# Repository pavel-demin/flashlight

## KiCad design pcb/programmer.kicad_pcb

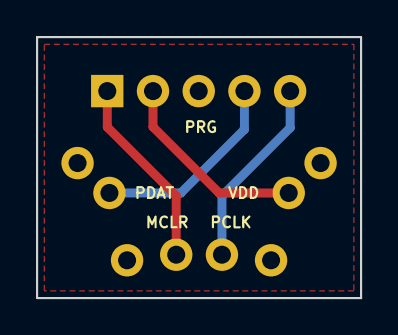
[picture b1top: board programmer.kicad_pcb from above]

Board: 2 copper layers, 18.0 x 14.5 mm, 9 parts (0 on the bottom side), 5 nets.

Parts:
MCLR: MCLR; PIN-1.0mm
PCLK: PCLK; PIN-1.0mm
PDAT: PDAT; PIN-1.0mm
PIN1, PIN2, PIN3, PIN4: PIN; PIN-1.0mm
PRG: PRG; Pin_Header_Straight_1x05_Pitch2.54mm
VDD: VDD; PIN-1.0mm

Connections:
GND: PIN1.1, PIN2.1, PIN3.1, PIN4.1, PRG.3
unnamed: PRG.2, VDD.1
unnamed: PCLK.1, PRG.5
unnamed: PDAT.1, PRG.4
unnamed: MCLR.1, PRG.1

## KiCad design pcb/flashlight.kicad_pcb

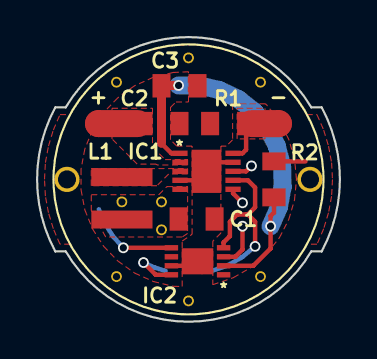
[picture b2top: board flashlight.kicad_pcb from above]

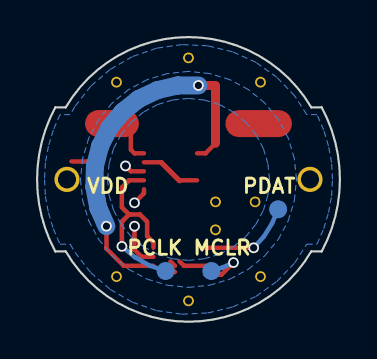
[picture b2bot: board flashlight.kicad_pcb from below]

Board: 2 copper layers, 16.8 x 15.8 mm, 25 parts (4 on the bottom side), 9 nets.

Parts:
+: +LED; PAD-1.5mm
-: LED-; PAD-1.5mm
C1: 10u; 0805
C2: 22u; 0805
C3: 1u; 0805
IC1: TPS61200; DRC
IC2: PIC10F320; MC
L1: 2.2u; XFL4020
MCLR: MCLR; PAD-1.0mm
PCLK: PCLK; PAD-1.0mm
PDAT: PDAT; PAD-1.0mm
PIN1, PIN2: PIN; PIN-1.0mm
R1: 2; 0805
R2: 1M; 0805
VDD: VDD; PAD-1.0mm
VIA1, VIA2, VIA3, VIA4, VIA5, VIA6, VIA7, VIA8, VIA9: VIA; VIA-0.6mm

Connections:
GND: C1.2, C2.2, C3.2, IC1.4, IC1.9, IC1.11, IC2.7, IC2.9, PIN1.1, PIN2.1, R1.2, R2.1, VIA4.1, VIA5.1, VIA6.1, VIA7.1, VIA8.1, VIA9.1
unnamed: IC1.3, L1.2
unnamed: +.1, C2.1, IC1.2
unnamed: C3.1, IC1.1, IC2.2, R2.2, VDD.1
unnamed: IC1.7, IC2.4, PCLK.1
unnamed: -.1, IC1.10, R1.1
unnamed: IC2.5, PDAT.1
unnamed: IC2.8, MCLR.1
SUPPLY: C1.1, IC1.5, IC1.6, IC1.8, IC2.3, L1.1, VIA1.1, VIA2.1, VIA3.1

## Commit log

2017-03-05 add flashlight.c
2017-03-05 set pcb radius to 7.9 mm
2017-03-05 add configuration bits
2017-03-06 add PIN-1.0mm
2017-03-06 add PIN part
2017-03-06 add two pins
2017-03-06 reduce VIA-0.6mm fonts
2017-03-06 move programming pads to bottom and add support extensions
2017-03-07 reduce radius of supply mask and move supply vias
2017-03-07 increase reference font size
2017-03-07 increase width of the vdd and led traces
2017-03-07 enlarge gnd zone
2017-03-07 reduce number of corners in circular zones
2017-03-08 add flashlight.asm
2017-03-09 remove extra empty line from flashlight.asm
2017-03-10 reduce delay in flashlight.asm
2017-03-11 add battery undervoltage protection
2017-03-11 set TRISA bit for RA3
2017-03-11 measure supply voltage 30 times per second
2017-03-11 replace CBLOCK with UDATA
2017-03-11 use timer interrupt for debouncing
2017-03-11 simplify mode switching
2017-03-12 set clock frequency to 1 MHz, remove interrupt code and add subroutines
2017-03-12 replace INTCON,2 with INTCON,TMR0IF
2017-03-12 replace busy loops with sleep
2017-03-13 fix TRISA and ANSELA, disable FVR after measurements
2017-03-13 replace 10k with 470k
2017-03-14 add flashlight-pwm.asm
2017-04-02 connect R2 to GND
2017-04-02 set RA1 to high in MODE1
2017-04-02 increase pulse width in MODE1
2019-02-18 replace parts.lib with parts_sklib.py
2019-02-18 fix pin function in parts_sklib.py
2019-02-18 remove do_erc from parts_sklib.py
2019-02-18 add ERC to flashlight.py
2019-02-18 add programmer.kicad_pcb
2019-02-19 use list comprehensions to create vias and nets
2019-02-20 add flashlight.tcl
2019-02-20 replace pins with args in flashlight.tcl
2019-02-20 use slash to split refs and pins in flashlight.tcl
2019-02-20 remove net codes from flashlight.tcl
2019-02-20 enlarge VIA-0.6mm fonts
2019-02-20 make part value optional in flashlight.tcl
2019-02-20 rename wires in flashlight.tcl
